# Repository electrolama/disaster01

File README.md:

# disaster01
overly blinky thing debuted at Hackaday Supercon 2019

Details at [electrolama.com/p/disaster01](https://electrolama.com/p/disaster01/).

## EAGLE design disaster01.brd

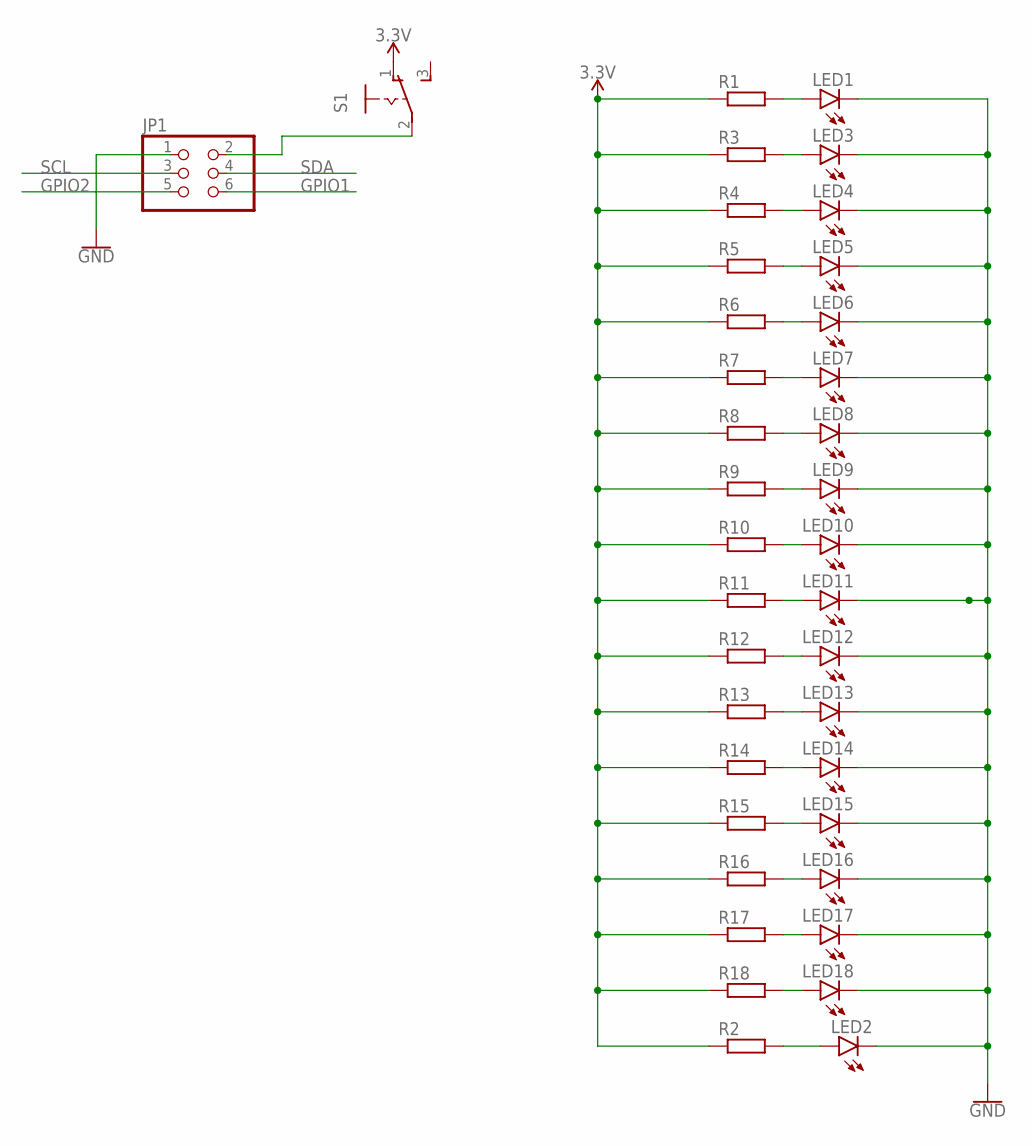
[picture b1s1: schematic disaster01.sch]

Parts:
JP1: PINHD-2X3; 2X03
LED1, LED3, LED4, LED5, LED6, LED7, LED8, LED9, LED10, LED11, LED12, LED13, LED14, LED15, LED16, LED17: LED3MM
LED2, LED18: LED10MM
R1, R2, R3, R4, R5, R6, R7, R8, R9, R10, R11, R12, R13, R14, R15, R16, R17, R18: R-EU_R0402; R0402
S1: 255SB

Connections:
3.3V: R1.1, R2.1, R3.1, R4.1, R5.1, R6.1, R7.1, R8.1, R9.1, R10.1, R11.1, R12.1, R13.1, R14.1, R15.1, R16.1, R17.1, R18.1, S1.1 (O)
GND: JP1.1, LED1.K (C), LED2.K (C), LED3.K (C), LED4.K (C), LED5.K (C), LED6.K (C), LED7.K (C), LED8.K (C), LED9.K (C), LED10.K (C), LED11.K (C), LED12.K (C), LED13.K (C), LED14.K (C), LED15.K (C), LED16.K (C), LED17.K (C), LED18.K (C)
GPIO1: JP1.6
GPIO2: JP1.5
unnamed: LED1.A, R1.2
unnamed: LED2.A, R2.2
unnamed: LED3.A, R3.2
unnamed: LED4.A, R4.2
unnamed: LED5.A, R5.2
unnamed: LED6.A, R6.2
unnamed: LED7.A, R7.2
unnamed: LED8.A, R8.2
unnamed: LED9.A, R9.2
unnamed: LED10.A, R10.2
unnamed: LED11.A, R11.2
unnamed: LED12.A, R12.2
unnamed: LED13.A, R13.2
unnamed: LED14.A, R14.2
unnamed: LED15.A, R15.2
unnamed: LED16.A, R16.2
unnamed: LED17.A, R17.2
unnamed: LED18.A, R18.2
unnamed: JP1.2, S1.2
SCL: JP1.3
SDA: JP1.4

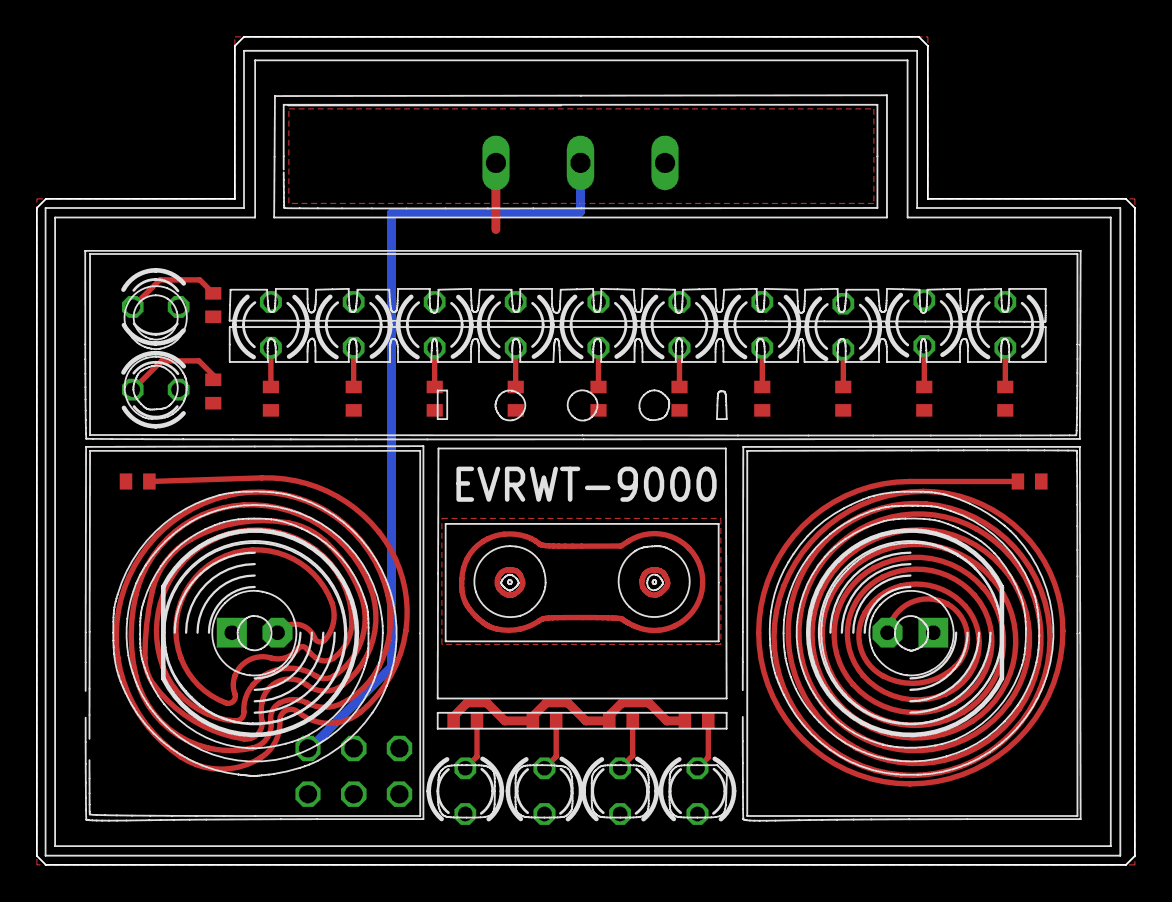
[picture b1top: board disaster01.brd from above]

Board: 2 copper layers, 61.0 x 46.0 mm, 38 parts (0 on the bottom side), 21 nets.

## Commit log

2019-11-15 initial commit, add design files

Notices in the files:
parts and their libraries:
SparkFun-PowerSymbols: Licensing: Creative Commons ShareAlike 4.0 International - https://creativecommons.org/licenses/by-sa/4.0
